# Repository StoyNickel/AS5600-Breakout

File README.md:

# AS5600-Breakout
PCB Design for AS5600 with Stemma QT/Qwiic Connectors

Contains KiCad files if you want to remix and Gerber, BOM, and position if you just want to build it. Gerbers, BOM, and position files are all setup and ready to go for JLCPCB.

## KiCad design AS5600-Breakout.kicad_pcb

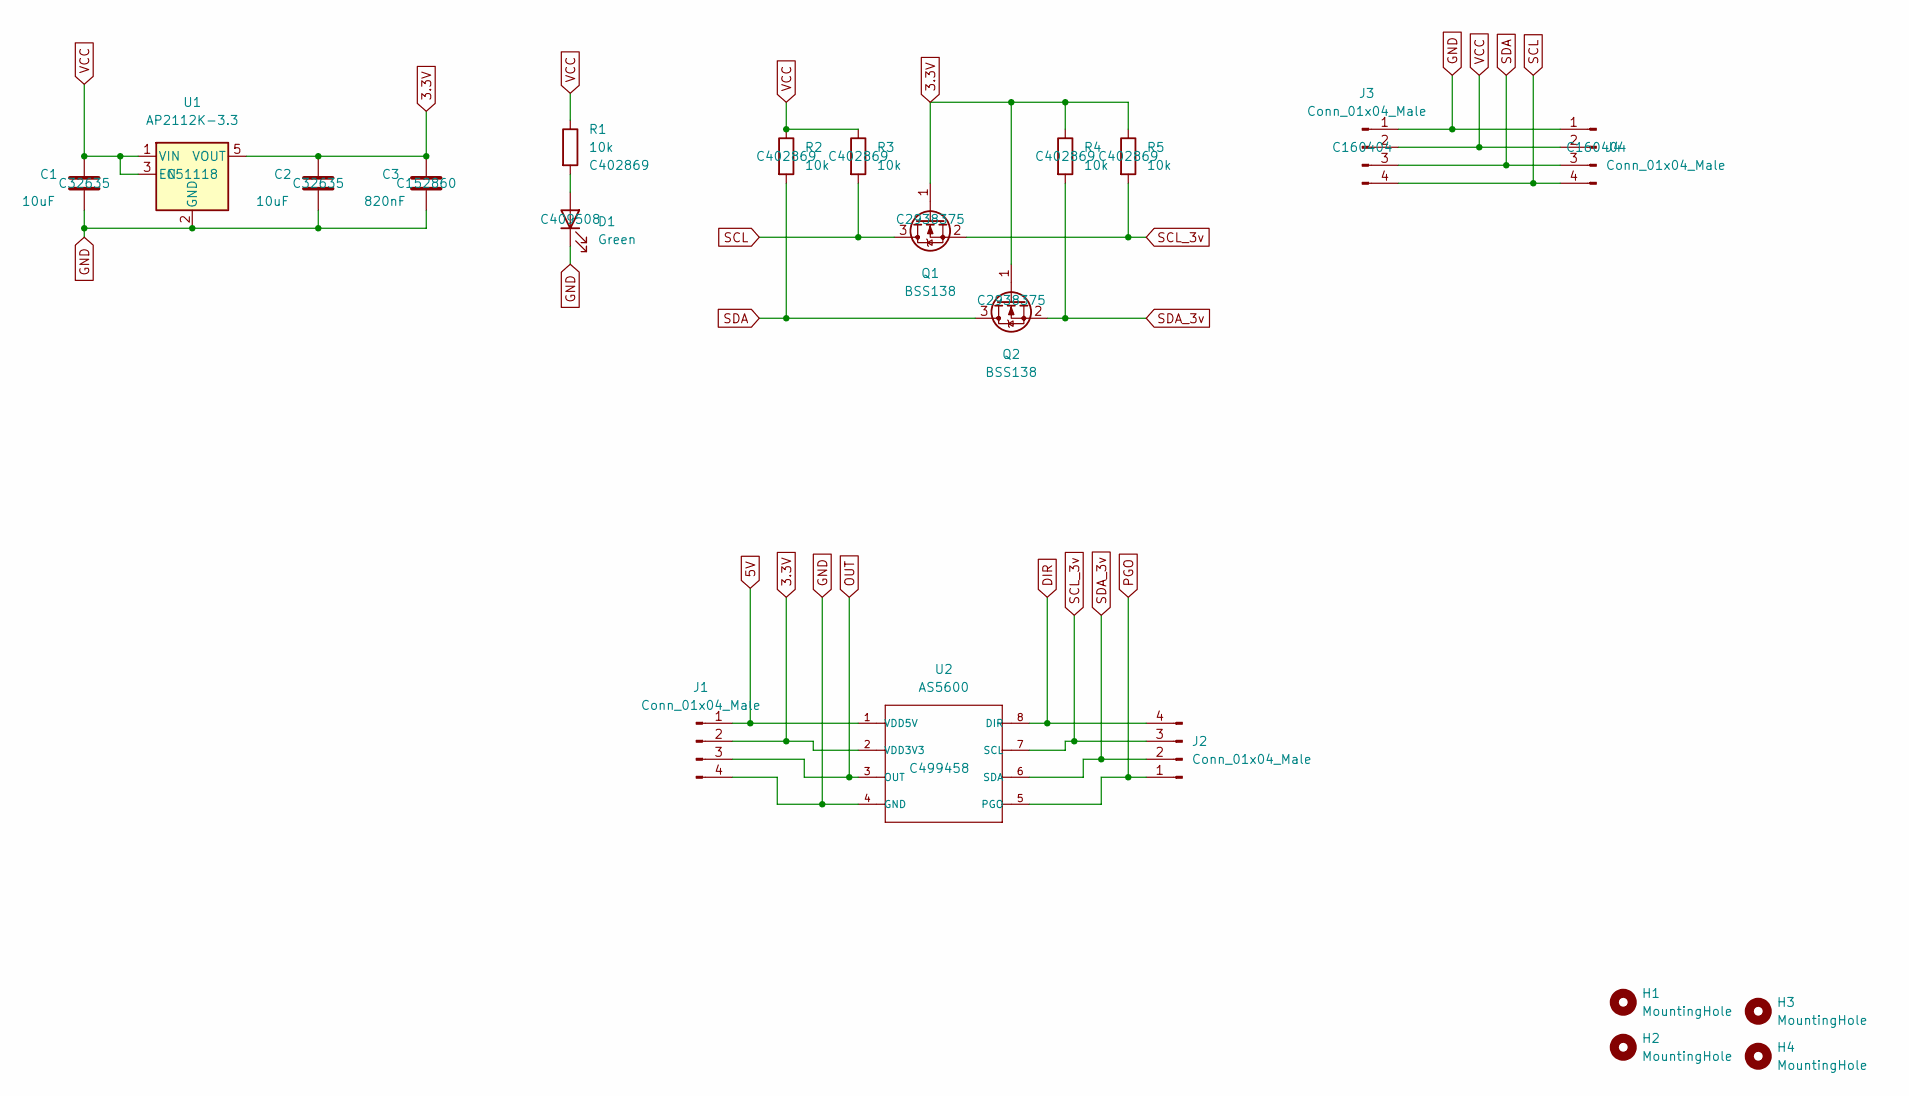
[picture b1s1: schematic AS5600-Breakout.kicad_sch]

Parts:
C1, C2: 10uF; C_0805_2012Metric; LCSC C32635
C3: 820nF; C_0805_2012Metric; LCSC C152860
D1: Green; LED_0603_1608Metric; LCSC C409508
H1, H2, H3, H4: MountingHole; MountingHole_2.5mm
J1, J2: Conn_01x04_Male; PinHeader_1x04_P2.54mm_Vertical
J3, J4: Conn_01x04_Male; JST_SH_SM04B-SRSS-TB_1x04-1MP_P1.00mm_Horizontal; LCSC C160404
Q1, Q2: BSS138; SOT-23; LCSC C2938375
R1, R2, R3, R4, R5: 10k; R_0603_1608Metric; LCSC C402869
U1: AP2112K-3.3; SOT-23-5; LCSC C51118
U2: AS5600; LCSC C499458

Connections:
3.3V: C2.1, C3.1, J1.2, Q1.1 (G), Q2.1 (G), R4.1, R5.1, U1.5 (VOUT), U2.2 (VDD3V3)
5V: J1.1, U2.1 (VDD5V)
DIR: J2.4, U2.8 (DIR)
GND: C1.2, C2.2, C3.2, D1.1 (K), J1.4, J3.1, J4.1, U1.2 (GND), U2.4 (GND)
unnamed: D1.2 (A), R1.2
OUT: J1.3, U2.3 (OUT)
PGO: J2.1, U2.5 (PGO)
SCL: J3.4, J4.4, Q1.3 (D), R3.2
SCL_3v: J2.3, Q1.2 (S), R5.2, U2.7 (SCL)
SDA: J3.3, J4.3, Q2.3 (D), R2.2
SDA_3v: J2.2, Q2.2 (S), R4.2, U2.6 (SDA)
VCC: C1.1, J3.2, J4.2, R1.1, R2.1, R3.1, U1.1 (VIN), U1.3 (EN)

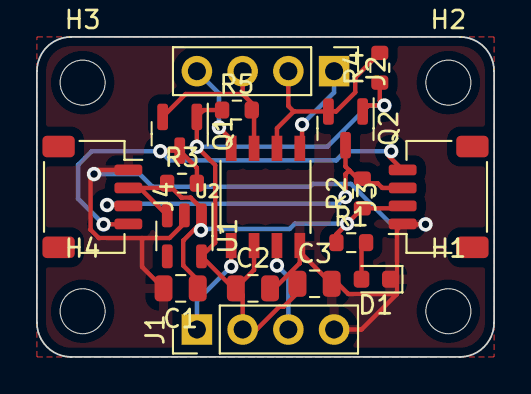
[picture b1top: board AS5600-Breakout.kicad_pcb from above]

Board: 2 copper layers, 25.4 x 17.8 mm, 21 parts (0 on the bottom side), 12 nets.

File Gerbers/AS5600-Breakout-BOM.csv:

Comment,Designator,Footprint,LCPCB Part #
10uF,"C1, C2",Capacitor_SMD:C_0805_2012Metric,C32635
820nF,C3,Capacitor_SMD:C_0805_2012Metric,C152860
Green,D1,LED_SMD:LED_0603_1608Metric,C409508
MountingHole,"H1, H2, H3, H4",MountingHole:MountingHole_2.5mm,
Conn_01x04_Male,"J1, J2",Connector_PinHeader_2.54mm:PinHeader_1x04_P2.54mm_Vertical,
Conn_01x04_Male,"J3, J4",Connector_JST:JST_SH_SM04B-SRSS-TB_1x04-1MP_P1.00mm_Horizontal,C160404
BSS138,"Q1, Q2",Package_TO_SOT_SMD:SOT-23,C2938375
10k,"R1, R2, R3, R4, R5",Resistor_SMD:R_0603_1608Metric,C402869
AP2112K-3.3,U1,Package_TO_SOT_SMD:SOT-23-5,C51118
AS5600,U2,AS5600,C499458

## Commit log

2023-01-14 Initial Build and upload
